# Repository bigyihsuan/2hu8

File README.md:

# 2hu8

The **2hu8** is a small, split keyboard meant for playing Touhou Project-type shmups.
Games that use a similar layout should also be playable (e.g. Undertale/Deltarune, other shmups, etc.)

## Layout

The board is split into two halves, both in the shape of the arrow key cluster.

| Half  | Keys                   |
| ----- | ---------------------- |
| Left  | Shift, Z, X, Esc, R, C |
| Right | Arrow keys             |

The left half houses the microcontroller, and is connected to the right half with a TRRS cable.

## Firmware

The 2hu8 is powered by QMK.

## Why is it 2hu8 when there's 10 keys?

The original design was to have 2 arrow key cluser-shaped boards for a total of 8 keys,
but then I realized that I forgot to add Esc (for pausing) and R
(in most Touhou games, pressing R in the pause menu quick restarts the run).

## License

The 2hu8 is licensed under [the MIT License](./LICENSE).

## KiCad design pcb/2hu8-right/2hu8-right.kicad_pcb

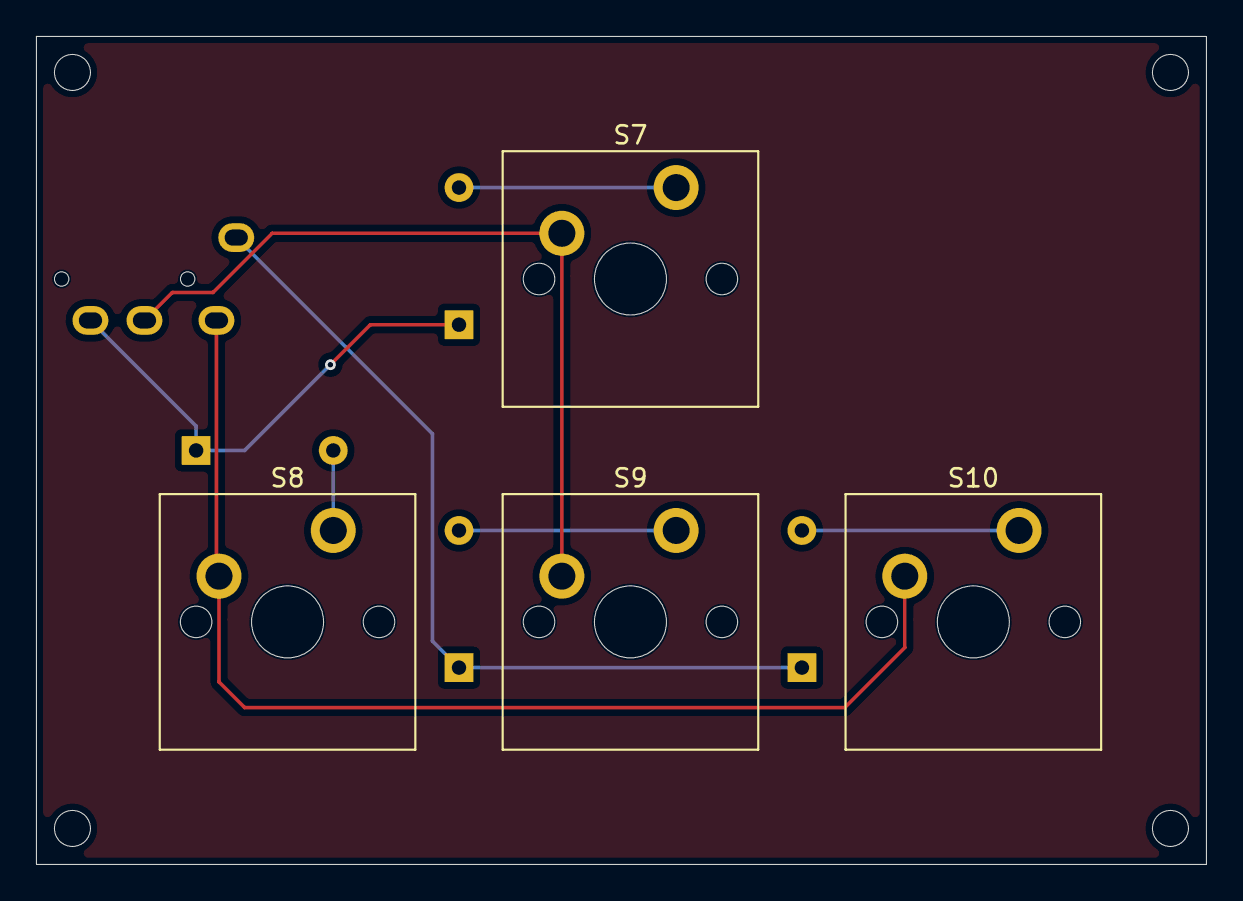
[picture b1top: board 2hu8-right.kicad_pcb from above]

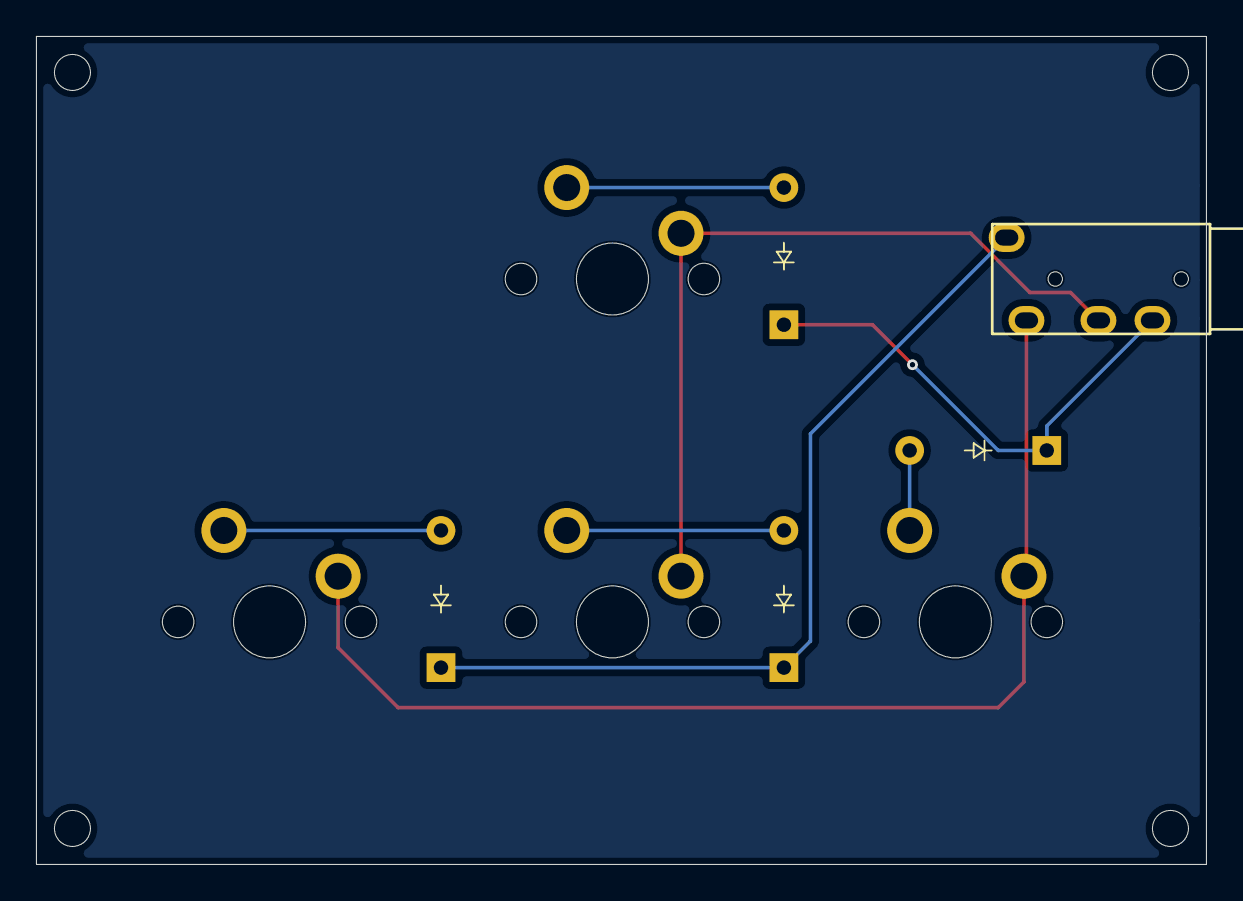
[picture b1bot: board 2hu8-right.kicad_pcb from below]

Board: 2 copper layers, 65.0 x 46.0 mm, 9 parts (5 on the bottom side), 8 nets.

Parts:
D7, D8, D9, D10: Diode_DO-35
S7, S8, S9, S10: MX_PCB_1.00u
U3: TRRS; TRRS_PJ-320A

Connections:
/Col 3: S7.1, S9.1, U3.3 (RING1)
/Col 4: S8.1, S10.1, U3.2 (TIP)
/Row 0: D7.1 (K), D8.1 (K), U3.4 (RING2)
/Row 1: D9.1 (K), D10.1 (K), U3.1 (SLEEVE)
unnamed: D7.2 (A), S7.2
unnamed: D8.2 (A), S8.2
unnamed: D9.2 (A), S9.2
unnamed: D10.2 (A), S10.2

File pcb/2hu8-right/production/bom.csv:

Designator,Footprint,Quantity,Value,LCSC Part #
"D10, D7, D8, D9",Diode_DO-35,4,~,
"S10, S7, S8, S9",MX_PCB_1.00u,4,~,
U3,TRRS_PJ-320A,1,TRRS,

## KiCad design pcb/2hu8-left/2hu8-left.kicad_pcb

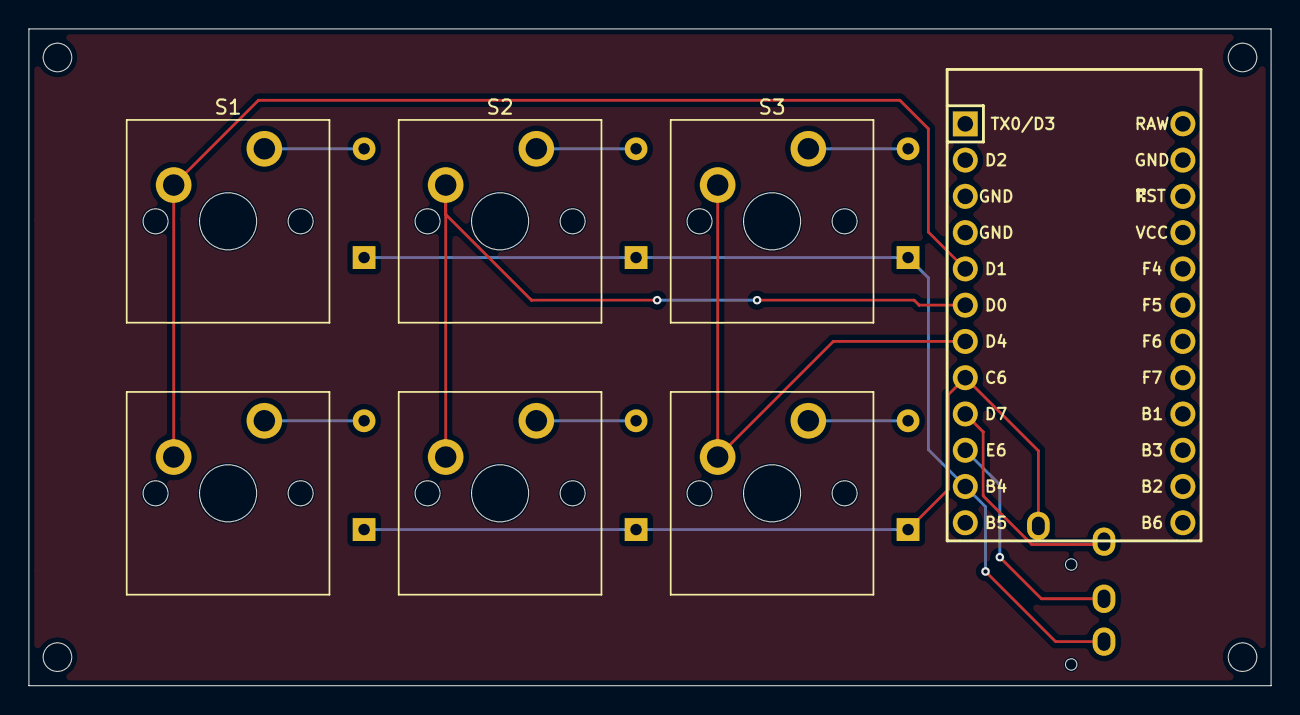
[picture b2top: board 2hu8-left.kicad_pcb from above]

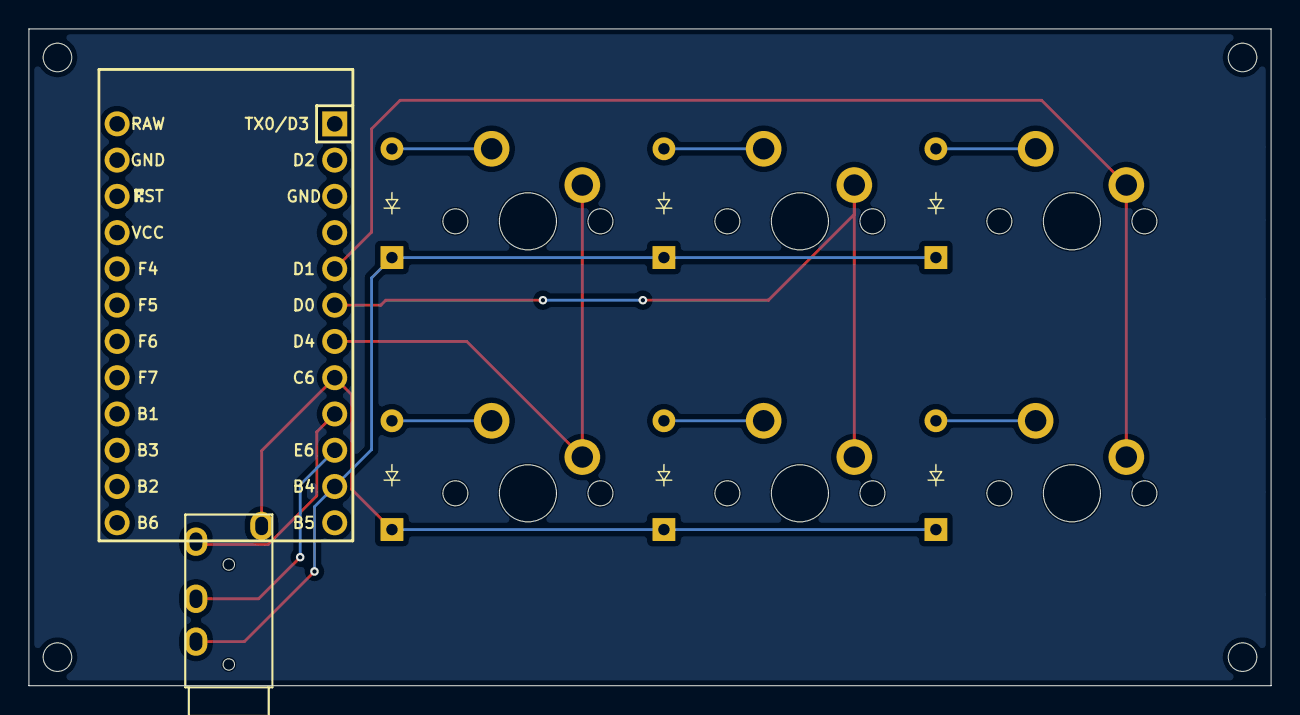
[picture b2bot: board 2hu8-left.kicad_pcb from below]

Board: 2 copper layers, 87.0 x 46.0 mm, 14 parts (7 on the bottom side), 13 nets.

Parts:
D1, D2, D3, D4, D5, D6: Diode_DO-35
S1, S2, S3, S4, S5, S6: MX_PCB_1.00u
U1: ProMicro; Arduino_Pro_Micro
U2: TRRS; TRRS_PJ-320A

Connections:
/Col 0: S1.1, S4.1, U1.5 (2/PD1)
/Col 1: S2.1, S5.1, U1.6 (3/PD0)
/Col 2: S3.1, S6.1, U1.7 (4/PD4)
/Col 3: U1.10 (7/PE6), U2.3 (RING1)
/Col 4: U1.9 (6/PD7), U2.2 (TIP)
/Row 0: D1.1 (K), D2.1 (K), D3.1 (K), U1.11 (8/PB4), U2.4 (RING2)
/Row 1: D4.1 (K), D5.1 (K), D6.1 (K), U1.8 (5/PC6), U2.1 (SLEEVE)
unnamed: D1.2 (A), S1.2
unnamed: D2.2 (A), S2.2
unnamed: D3.2 (A), S3.2
unnamed: D4.2 (A), S4.2
unnamed: D5.2 (A), S5.2
unnamed: D6.2 (A), S6.2

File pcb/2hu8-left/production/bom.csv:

Designator,Footprint,Quantity,Value,LCSC Part #
"D1, D2, D3, D4, D5, D6",Diode_DO-35,6,~,
"S1, S2, S3, S4, S5, S6",MX_PCB_1.00u,6,~,
U1,Arduino_Pro_Micro,1,ProMicro,
U2,TRRS_PJ-320A,1,TRRS,

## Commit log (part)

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2026-06-26 initial README and some initial notes
2026-06-26 start pcb
2026-06-26 add submodules for kicad
2026-06-26 add footprint lib
2026-06-26 add keebio parts
2026-06-26 add keebio footprint library
2026-06-26 add keebio component symbol submodule
2026-06-26 add keebio component symbols
2026-06-26 remove submodules
2026-06-26 add gitignore
2026-06-26 start schematic
2026-06-28 change in design to 10 keys
2026-06-28 restart pcb, as kicad does not support split pcb workflow well
2026-06-28 reinit pcb project
2026-06-30 final initial design for the boards
2026-06-30 add keyboard layout editor json files
2026-06-30 skeleton for qmk firmware
